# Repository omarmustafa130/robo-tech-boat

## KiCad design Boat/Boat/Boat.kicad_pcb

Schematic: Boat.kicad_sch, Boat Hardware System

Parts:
C1: 4.7nF; C_0603_1608Metric
C2, C20: 10uF/16V; C_0603_1608Metric
C3, C4, C14, C15, C16, C19, C21: 0.1uF; C_0603_1608Metric
C5: 100uF/63V/20%/10x13MM/Low_ESR/RM5; C_0603_1608Metric
C6: 100uF/100V/10%/X7R/C0603; C_0603_1608Metric
C7: 100nf/100V/10%/X7R/C0603; C_0603_1608Metric
C8, C11, C12, C32, C33, C34: 22uF/6.3V/20%/X5R/C0603; C_0603_1608Metric
C9: 12pF/50V/5%/COG/C0402; C_0402_1005Metric
C10: 470uF/10V/RVT1A471M0607; CP_Elec_6.3x7.7
C13, C41, C49, C50, C52, C53, C56, C58, C59, C60: 100nF; C_0603_1608Metric
C17, C18: 18pF; C_0402_1005Metric
C22, C24, C51, C57: 10nF; C_0603_1608Metric
C23: 4.7uF; C_0603_1608Metric
C25: 22nF; C_0603_1608Metric
C26, C27: 6.8nF; C_0603_1608Metric
C28: 1nF/2kV; C_0603_1608Metric
C29, C31: 4.7uF/6.3V (10%); C_0603_1608Metric
C30, C35: 0.1uF/50V (10%); C_0603_1608Metric
C36, C37, C38, C39, C42, C43, C46, C47, C48: 2.2uF; C_0603_1608Metric
C40: 1uF/10V/10%/X5R/C0603; C_0603_1608Metric
C44, C45: 10pF; C_0603_1608Metric
D1: SMAJ58A; D_SMA
D2: LED/RED/0603; LED_0603_1608Metric
D3: SS310; D_SMA
D4, D5, D6, D7, D8, D10, D11, D20: 1N4148W(SOD-123); 1N4148W_SODFL3816X120N
D9: 1N5822; D_DO-201AD_P15.24mm_Horizontal
D15, D17, D18: LED; LED_0603_1608Metric
D16: NUP2105L; SOT-23
IC1, IC2: SMD_IC_SY8089AAAC; SY80B9AAAC_SOT95P285X140-5N; Mouser Part Number 909-SMDICSY8089AAAC
IC3, IC4: MIC2099-1YMTTR; MIC2099_SON50P160X160X60-7N-D; Manufacturer_Part_Number MIC2099-1YMTTR
J1: J1B1211CCD; Mouser Part Number 950-J1B1211CCD
J2, J3, J6, J13, J14, J17, J18, J19: Screw_Terminal_01x02; Altech_AK100_1x02_P5.00mm
J4, J16: Screw_Terminal_01x03; Altech_AK100_1x03_P5.00mm
J7, J8, J9, J10, J15: Screw_Terminal_01x06; Altech_AK100_1x06_P5.00mm
J11, J12: Conn_01x03_Pin; JST_EH_B3B-EH-A_1x03_P2.50mm_Vertical
J22: USB_C_Receptacle_USB2.0_16P; USB_C_Receptacle_HRO_TYPE-C-31-M-12
K1, K2, K3, K4, K5, K6, K7, K8: SRD-05VDC-SL-C; RELAY_SRD-05VDC-SL-C
L1: 600R; R_0402_1005Metric
L2: 33uH/SL0630-330M; SL0630-330M
L3, L4: 2.2uH/1.5A/DCR=72mR/20%/3.00x3.00x1.50mm/CD32(NR3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; IND_NR3015T2R2M
L6: 120R 3A; L_0603_1608Metric
Q1: WPM2015-3/TR; WPM2015-3TR_SOT95P240X130-3N
Q2, Q3, Q4, Q5: SS8050-G(RANGE:120-200); SS8050_SOT95P240X115-3N
Q6: BC817; SOT-23
R1, R2, R10, R11, R12: 330R; R_0603_1608Metric
R3: 2.2k/R0402; R_0402_1005Metric
R4: 0.03R/1%/R1206; R_1206_3216Metric
R5: 4.7R/R0402; R_0402_1005Metric
R6: 5.23k/1%/R0402; R_0402_1005Metric
R7: 30.1k/1%/R0402; R_0402_1005Metric
R8, R56: 220k/R0402; R_0402_1005Metric
R9, R57: 49.9k/1%/R0402; R_0402_1005Metric
R13, R41: 22.1k (5%); R_0603_1608Metric
R14, R42: 47.5k (5%); R_0603_1608Metric
R15, R17, R48, R53, R54, R55: 100k; R_0603_1608Metric
R16: 1M; R_0402_1005Metric
R18, R43: 2k (5%); R_0603_1608Metric
R19, R27, R28, R29, R30: 0R; R_0402_1005Metric
R20, R21, R22, R23, R24, R25: 20R; R_0402_1005Metric
R26: 12.4k/1%; R_0402_1005Metric
R31, R32, R33, R34: 49R9/1%; R_0402_1005Metric
R35: 10R/1%; R_0402_1005Metric
R36, R37: 330R; R_0402_1005Metric
R38, R58: 100R/R0402; R_0402_1005Metric
R39, R40: 10k; R_0603_1608Metric
R44, R45, R49, R59: 10k (5%); R_0603_1608Metric
R46, R47, R60, R61: 0R (5%); R_0603_1608Metric
R50: 12k; R_0603_1608Metric
R51: 120R; R_0402_1005Metric
R52, R68: 10k; R_0402_1005Metric
R67: 1k; R_0402_1005Metric
R86: 10k/R0402; R_0402_1005Metric
S1: MS-22D28-G020; MS22D28G020; Manufacturer_Part_Number MS-22D28-G020
SW1, SW3, SW4: TS665CJ; SW_PUSH_6mm
SW2, SW5: SW_DPST_x2; Power Switch - RS601HL-1010011BB
T1, T2, T3, T4, T5, T6, T7, T9: LMUN2235LT1G(SOT-23); LMUN2235LT1G
TX4138(ESOIC-8)1: TX4138_SOIC127P600X165-9N
U1, U13: CP2102N-Axx-xQFN28; QFN-28-1EP_5x5mm_P0.5mm_EP3.35x3.35mm
U2, U3: ESP32-WROOM-32
U4: W5500; LQFP-48_7x7mm_P0.5mm
U5, U7: MCP23017T-E/ML; MCP23017T-E_ML_QFN65P600X600X100-29N-D
U6: SN65HVD233; SOIC-8_3.9x4.9mm_P1.27mm
U8: USBLC6-2SC6; SOT-23-6
U9: SPX3819M5-L-3-3; SOT-23-5
U10: USB2514B_Bi; QFN-36-1EP_6x6mm_P0.5mm_EP3.7x3.7mm
Y1: HSO321S 24MHZ 3.3V -40~+85℃; HSO321S
Y2: XRCGB24M000F2P00R0; OSC_XRCGB24M000F2P00R0; PARTREV N/A

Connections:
3.3V_2: S1.3 (NC_1)
+3.3V: J1.10, J1.12
+3.3VA: C2.1, C3.1, C4.1, C14.1, C15.1, C16.1, C19.1, L1.1, R31.1, R33.1, R35.1, U4.4 (AVDD), U4.8 (AVDD), U4.11 (AVDD), U4.15 (AVDD), U4.17 (AVDD), U4.21 (AVDD)
+3.3V_1: C11.1, C12.1, C29.2, C30.2, L3.2, R8.2, R43.2, R68.1, R86.1, U1.6 (VDD), U1.7 (VREGIN), U3.2 (VDD), U7.9 (VDD)
+3.3V_2: C13.1, C20.1, C21.1, C31.2, C33.1, C34.1, C35.2, C43.1, C48.1, C49.1, C52.1, C56.1, C58.1, C59.1, C60.1, D18.2 (A), J16.1, L1.2, L4.2, R18.2, R56.2, U2.2 (VDD), U4.28 (VDD), U5.9 (VDD), U6.3 (VCC), U9.5 (OUT), U10.5 (VDDA33), U10.10 (VDDA33), U10.15 (VDD33), U10.23 (VDD33), U10.26 (RESET_N), U10.29 (VDDA33), U10.36 (VDDA33), U13.6 (VDD), U13.7 (VREGIN)
+5V: C8.1, C32.1, D4.1 (K), D5.1 (K), D6.1 (K), D7.1 (K), D8.1 (K), D9.1 (K), D10.1 (K), D11.1 (K), D20.1 (K), IC1.1 (EN), IC1.4 (IN), IC2.1 (EN), IC2.4 (IN), K1.A1, K2.A1, K3.A1, K4.A1, K5.A1, K6.A1, K7.A1, K8.A1, Q1.3 (S), R3.1
+5V_EXT: C9.1, C10.1, D9.2 (A), L2.2, Q1.2 (G), R7.1
+5V_HOST_Filtered: C37.1, C38.1, C46.1, C47.1, IC3.6 (VIN), IC4.6 (VIN), L6.2, R15.1, R39.1, R40.1, U9.1 (IN)
+5V_PORT1: C39.1, D15.2 (A), IC3.1 (VOUT)
+5V_PORT2: C42.1, D17.2 (A), IC4.1 (VOUT)
+5V_USB: Q1.1 (D), R13.1, R41.1
+12V: C5.1, C6.1, D1.1 (A1), J2.1, J3.1, R4.2, TX4138(ESOIC-8)1.3 (VIN)
/1V2O: C22.1, U4.22 (1V2O)
/ACTLED: R37.2, U4.27 (ACTLED)
/EXRES1: R26.1, U4.10 (EXRES1)
/ILIM: R4.1, TX4138(ESOIC-8)1.2 (ILIM), TX4138(ESOIC-8)1.9 (ILIM)
/LINKLED: R36.2, U4.25 (LINKLED)
/RXN: R29.1, U4.5 (RXN)
/RXP: R30.1, U4.6 (RXP)
/TOCAP: C23.1, U4.20 (TOCAP)
/TXN: R27.1, U4.1 (TXN)
/TXP: R28.1, U4.2 (TXP)
/VBUS_DET: R15.2, R17.1, U9.3 (EN), U10.27 (VBUS_DET)
/XI: C17.1, R16.1, U4.30 (XI/CLKIN), Y1.1
/XO: R16.2, R19.1, U4.31 (XO)
BOOT1: Q3.1 (C), R38.1, U3.25 (IO0)
BOOT2: Q5.1 (C), R58.1, U2.25 (IO0)
CGND: C28.2, J1.8 (GND), J1.13, J1.14
CS: R20.1, U2.36 (IO22)
D: U2.29 (IO5), U3.29 (IO5), U6.1 (D)
D+: J22.A6 (D+), J22.B6 (D+), U8.6 (I/O1)
D-: J22.A7 (D-), J22.B7 (D-), U8.4 (I/O2)
DTR1: Q3.3 (E), R44.1, U1.28 (~DTR)
DTR2: Q5.3 (E), R49.1, U13.28 (~DTR)
ESP_3V3: U5.15 (A0), U5.16 (A1), U5.17 (A2)
ESP_EN: C40.1, Q2.1 (C), Q4.1 (C), R86.2, SW4.1, U2.3 (EN), U3.3 (EN)
FUAL2PIN: U3.6 (IO34)
FUALPIN: U3.7 (IO35)
GND: C1.2, C2.2, C3.2, C4.2, C5.2, C6.2, C8.2, C10.2, C11.2, C12.2, C13.2, C14.2, C15.2, C16.2, C17.2, C18.2, C19.2, C20.2, C21.2, C22.2, C23.2, C24.1, C25.2, C28.1, C29.1, C30.1, C31.1, C32.2, C33.2, C34.2, C35.1, C36.2, C37.2, C38.2, C39.2, C40.2, C41.2, C42.2, C43.2, C44.2, C45.2, C46.2, C47.2, C48.2, C49.2, C50.2, C51.2, C52.2, C53.2, C56.2, C57.2, C58.2, C59.2, C60.2, D1.2 (A2), D2.1 (K), D3.2 (A), D16.3 (A), IC1.2 (GND), IC2.2 (GND), IC3.5 (GND), IC3.7 (EP), IC4.5 (GND), IC4.7 (EP), J2.2, J3.2, J7.1, J7.3, J7.5, J8.1, J8.3, J8.5, J9.1, J9.3, J9.5, J10.1, J10.3, J10.5, J11.2, J12.3, J15.1, J15.3, J15.5, J16.3, J22.A1 (GND), J22.A12 (GND), J22.B1 (GND), J22.B12 (GND), Q6.3 (E), R1.1, R2.1, R6.2, R9.2, R10.1, R11.1, R12.2, R14.2, R17.2, R26.2, R42.2, R48.2, R50.1, R52.1, R53.2, R54.2, R55.2, R57.2, SW1.2, SW2.2 (B), SW3.2, SW4.2, SW5.2 (B), T1.2 (E), T2.2 (E), T3.2 (E), T4.2 (E), T5.2 (E), T6.2 (E), T7.2 (E), T9.2 (E), TX4138(ESOIC-8)1.4 (GND), U1.3 (GND), U1.29 (GND), U2.1 (GND), U2.15 (GND), U2.38 (GND), U2.39 (GND), U3.1 (GND), U3.15 (GND), U3.38 (GND), U3.39 (GND), U4.3 (AGND), U4.9 (AGND), U4.14 (AGND), U4.16 (AGND), U4.19 (AGND), U4.29 (GND), U4.48 (AGND), U5.10 (VSS), U5.29 (GND), U6.2 (GND), U7.10 (VSS), U7.15 (A0), U7.16 (A1), U7.17 (A2), U7.29 (GND), U8.2 (GND), U9.2 (GND), U10.11 (TEST), U10.37 (VSS), U13.3 (GND), U13.29 (GND), Y1.2, Y1.4, Y2.2, Y2.4
GNDPWR: C1.1, J22.S1 (SHIELD)
H: D16.1 (K), J11.1, R51.1, U6.7 (CANH)
INT: R24.1, U2.16 (IO13)
IO21/WIRE_SDA_1: U3.21 (SDO/SD0), U7.13 (SDA)
IO21/WIRE_SDA_2: U2.21 (SDO/SD0), U5.13 (SDA)
IO22/WIRE_SCL_1: U3.22 (SDI/SD1), U7.12 (SCK)
IO22/WIRE_SCL_2: U2.22 (SDI/SD1), U5.12 (SCK)
L: D16.2 (K), J11.3, R51.2, U6.6 (CANL)
MISO: R22.1, U2.31 (IO19)
MOSI: R23.1, U2.37 (IO23)
unnamed: C7.1, R5.2
unnamed: C18.1, R19.2, Y1.3
unnamed: C24.2, J1.5, R32.2, R34.2
unnamed: C25.1, J1.2, R35.2
unnamed: C26.1, R29.2, R32.1
unnamed: C26.2, J1.6
unnamed: C27.1, R30.2
unnamed: C27.2, J1.4, R34.1
unnamed: D2.2 (A), R3.2
unnamed: C7.2, D3.1 (K), L2.1, TX4138(ESOIC-8)1.1 (SW)
unnamed: D4.2 (A), K2.A2, T1.3 (C)
unnamed: D5.2 (A), K5.A2, T2.3 (C)
unnamed: D6.2 (A), K3.A2, T3.3 (C)
unnamed: D7.2 (A), K6.A2, T4.3 (C)
unnamed: D8.2 (A), K4.A2, T5.3 (C)
unnamed: D10.2 (A), K7.A2, T6.3 (C)
unnamed: D11.2 (A), K8.A2, T7.3 (C)
unnamed: D15.1 (K), R1.2
unnamed: D17.1 (K), R2.2
unnamed: D18.1 (K), R12.1
unnamed: D20.2 (A), K1.A2, T9.3 (C)
unnamed: IC1.5 (FB), R8.1, R9.1
unnamed: IC1.3 (LX), L3.1
unnamed: IC2.5 (FB), R56.1, R57.1
unnamed: IC2.3 (LX), L4.1
unnamed: IC3.2 (ILIMIT), R10.2
unnamed: IC4.2 (ILIMIT), R11.2
unnamed: J1.1, R28.2, R33.2
unnamed: J1.3, R27.2, R31.2
unnamed: J1.9, R37.1
unnamed: J1.11, R36.1
unnamed: J6.1, K1.NO
unnamed: J6.2, K1.COM
unnamed: J13.1, K2.NO
unnamed: J13.2, K2.COM
unnamed: J14.1, K3.NO
unnamed: J14.2, K3.COM
unnamed: J17.1, K4.NO
unnamed: J17.2, K4.COM
unnamed: J18.1, K5.NO
unnamed: J18.2, K5.COM
unnamed: J19.1, K6.NO
unnamed: J19.2, K6.COM
unnamed: Q2.2 (B), R44.2
unnamed: Q3.2 (B), R45.2
unnamed: Q4.2 (B), R49.2
unnamed: Q5.2 (B), R59.2
unnamed: Q6.2 (B), R67.2
unnamed: R38.2, SW1.1
unnamed: R58.2, SW3.1
unnamed: S1.2 (COM_1), U6.8 (Rs)
unnamed: R52.2, S1.1 (NO_1)
unnamed: R5.1, TX4138(ESOIC-8)1.8 (BS)
unnamed: C9.2, R6.1, R7.2, TX4138(ESOIC-8)1.5 (FB)
unnamed: R41.2, R42.1, U1.8 (VBUS)
unnamed: R43.1, U1.9 (~RST)
unnamed: R22.2, U4.34 (MISO)
unnamed: R23.2, U4.35 (MOSI)
unnamed: R21.2, U4.33 (SCLK)
unnamed: R24.2, U4.36 (~INT)
unnamed: R25.2, U4.37 (~RST)
unnamed: R20.2, U4.32 (~SCS)
unnamed: C41.1, U9.4 (BP)
unnamed: C53.1, C57.1, U10.14 (CRFILT)
unnamed: R55.1, U10.25 (HS_IND/CFG_SEL1)
unnamed: C50.1, C51.1, U10.34 (PLLFILT)
unnamed: R50.2, U10.35 (RBIAS)
unnamed: R48.1, U10.24 (SCL/SMBCLK/CFG_SEL0)
unnamed: R53.1, U10.22 (SDA/SMBDATA/NON_REM1)
unnamed: R54.1, U10.28 (SUSP_IND/LOCAL_PWR/NON_REM0)
unnamed: R13.2, R14.1, U13.8 (VBUS)
unnamed: R18.1, U13.9 (~RST)
OCS_N1: IC3.3 (~FAULT), U10.13 (OCS_N1)
OCS_N2: IC4.3 (~FAULT), U10.17 (OCS_N2)
PRTPWR1: IC3.4 (ENABLE), R39.2, SW2.1 (A), U10.12 (PRTPWR1/BC_EN1)
PRTPWR2: IC4.4 (ENABLE), R40.2, SW5.1 (A), U10.16 (PRTPWR2/BC_EN2)
PUDUNE1: J4.1, K7.NO
PUL1: J7.6, U3.14 (IO12)
PUL1_3: J15.6, U2.10 (IO25)
PUL2: J8.6, U3.16 (IO13)
PUL3: J9.6, U3.13 (IO14)
PUL4: J10.6, U3.23 (IO15)
PUT: J16.2, U2.4 (SENSOR_VP)
PUUP: J4.3, K7.COM, K8.COM
PUUP1: J4.2, K8.NO
R: U2.26 (IO4), U3.26 (IO4), U6.4 (R)
R1: T9.1 (B), U5.1 (GPB0)
R2: T1.1 (B), U5.2 (GPB1)
R3: T2.1 (B), U5.3 (GPB2)
R4: T4.1 (B), U5.4 (GPB3)
R5: T3.1 (B), U5.5 (GPB4)
R6: T5.1 (B), U5.6 (GPB5)
R7: T6.1 (B), U5.7 (GPB6)
R8: T7.1 (B), U5.8 (GPB7)
RST: R25.1, U2.14 (IO12)
RTS1: Q2.3 (E), R45.1, U1.24 (~RTS)
RTS2: Q4.3 (E), R59.1, U13.24 (~RTS)
RX0_1: R47.1, U3.34 (RXD0/IO3)
RX0_2: R61.1, U2.34 (RXD0/IO3)
RXD1: R46.2, U1.25 (RXD)
RXD2: R60.2, U13.25 (RXD)
RXDS: Q6.1 (C), R68.2, U2.27 (IO16), U3.27 (IO16)
SBUSIN: J12.1, R67.1
SCLK: R21.1, U2.30 (IO18)
TX0_1: R46.1, U3.35 (TXD0/IO1)
TX0_2: R60.1, U2.35 (TXD0/IO1)
TXD1: R47.2, U1.26 (TXD)
TXD2: R61.2, U13.26 (TXD)
USBDM_UP: U8.3 (I/O2), U10.30 (USBDM_UP)
USBDP_UP: U8.1 (I/O1), U10.31 (USBDP_UP)
USB_PORT1_M: U1.5 (D-), U10.1 (USBDM_DN1/PRT_DIS_M1)
USB_PORT1_P: U1.4 (D+), U10.2 (USBDP_DN1/PRT_DIS_P1)
USB_PORT2_M: U10.3 (USBDM_DN2/PRT_DIS_M2), U13.5 (D-)
USB_PORT2_P: U10.4 (USBDP_DN2/PRT_DIS_P2), U13.4 (D+)
VBUS_DTS: C36.1, J22.A4 (VBUS), J22.A9 (VBUS), J22.B4 (VBUS), J22.B9 (VBUS), L6.1, U8.5 (VBUS)
XTAL_IN: C45.1, U10.33 (XTALIN/CLKIN), Y2.3
XTAL_OUT: C44.1, U10.32 (XTALOUT), Y2.1
dir1: J7.4, U7.1 (GPB0)
dir1_3: J15.4, U2.11 (IO26)
dir2: J8.4, U7.3 (GPB2)
dir3: J9.4, U7.5 (GPB4)
dir4: J10.4, U7.7 (GPB6)
enable_dc: J15.2, U2.12 (IO27)
enable_stp1: J7.2, U7.2 (GPB1)
enable_stp2: J8.2, U7.4 (GPB3)
enable_stp3: J9.2, U7.6 (GPB5)
enable_stp4: J10.2, U7.8 (GPB7)

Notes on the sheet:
RELAYS
SBUS - NEMA - Relays - Ethernet - DC - Potentiometer
+3.3V
DC Motor + Pot
12Vin
ETHERNET
GPIO EXPANDER
DC-DC Converter 3.3V
SBUS
Power Supply
BOOT 2
USB-TTL 2
ESP32-WROOM32
STEPPER MOTORS
BOOT
USB-TTL
USB HUB
+12V
RESET
GPIO EXPANDER 2
HOST USB-C
+5V
Steppers + Fuel
CAN

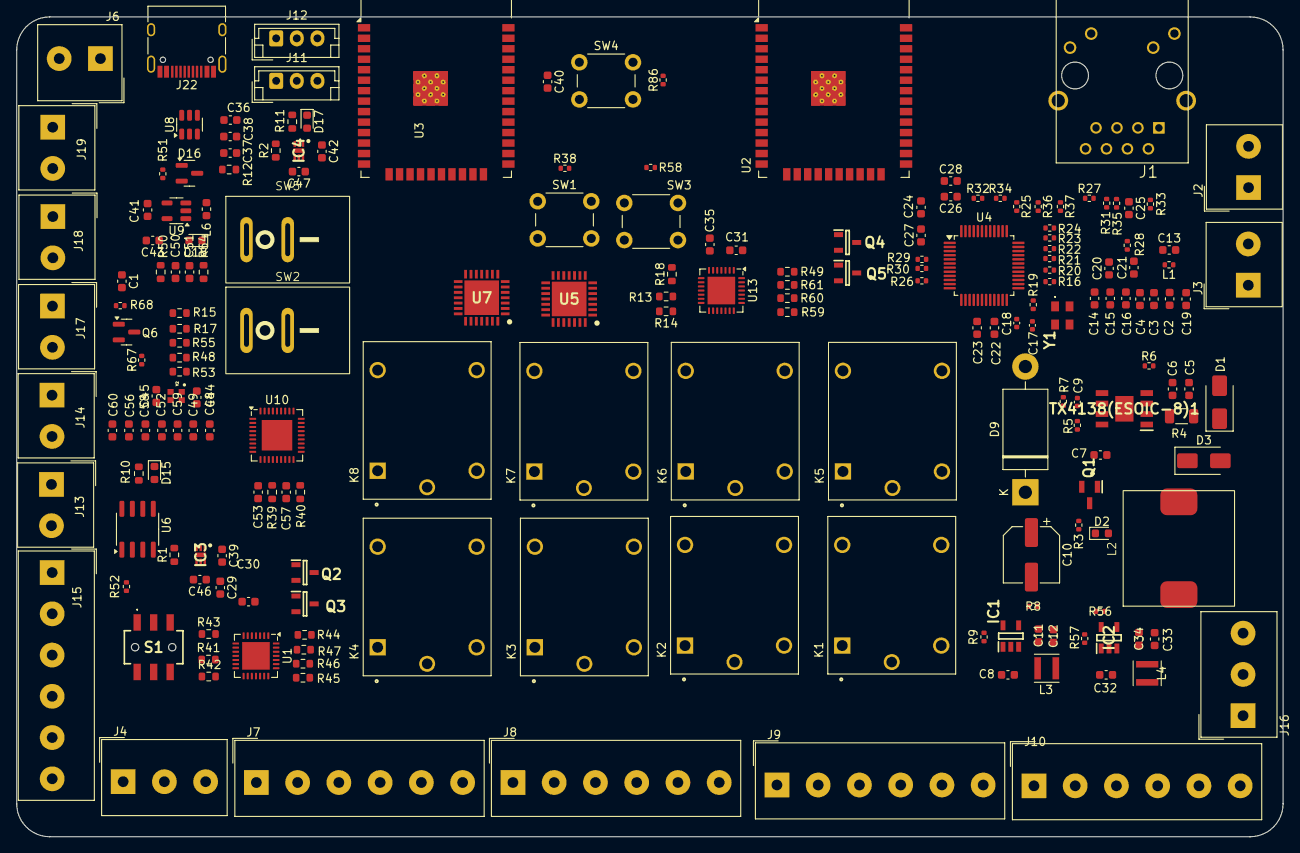
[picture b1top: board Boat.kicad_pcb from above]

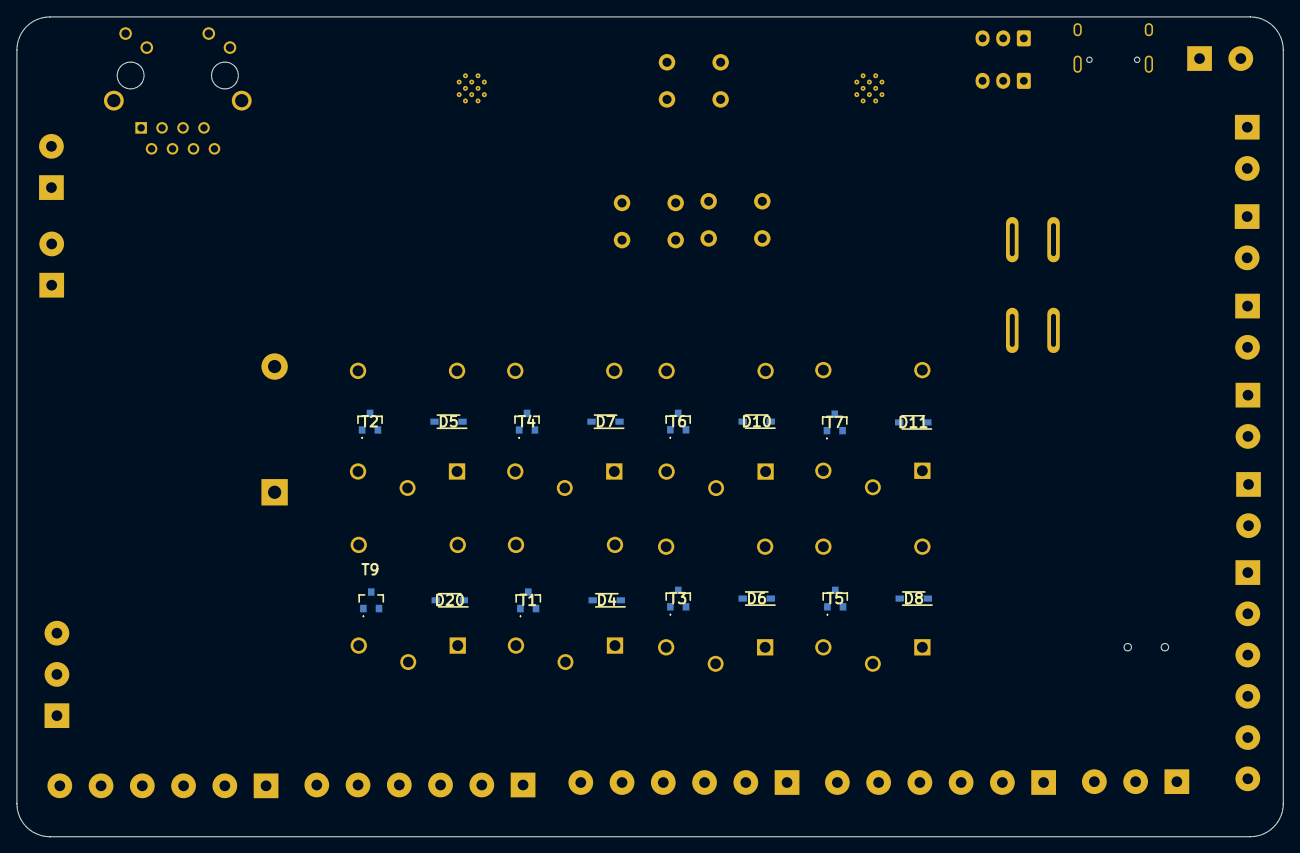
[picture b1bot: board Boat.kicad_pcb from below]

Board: 2 copper layers, 153.5 x 99.4 mm, 208 parts (16 on the bottom side), 173 nets, no tracks yet.

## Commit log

2025-05-22 Layout
